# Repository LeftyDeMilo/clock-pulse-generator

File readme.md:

Breadboard Clock Pulse Generator with manual and automatic operating modes.
In manual mode the circuit operates as a debounced button. In automatic mode
it operates as a square wave generator. You could bear through a preset list
of frequencies in a range from 0.1 Hz to 97 Hz.

# Terminal

To check ATtiny24 fuses (and the MCU reaction) you could use `avrdude`.

```sh
$ avrdude -p t24 -c usbasp
```

Brandnew ATtiny24 _20SSU_ responses `Fuses OK (E:FF, H:DC, L:E2)`,
_20PU_ – `Fuses OK (E:FF, H:DF, L:62)`.

Preset fuses:

```sh
$ avrdude -p t24 -c usbasp -U lfuse:w:0xE2:m -U hfuse:w:0xDD:m -U efuse:w:0xFE:m
```

# Arduino IDE

Choose the proper MCU:

Tools > Board > DIY ATtiny > ATtiny24

Choose the compilation settings

Tools >

* Use Bootloader: "No (ISP Programmer Upload)"
* Processor Speed: "8MHz Internal Oscillator"
* Millis, Tone Support: "Millis Available, No Tone"
* Millis Accuracy: "Better Or Equal 0.1% Error (Highest Code Use)"
* Processor Version: "ATtiny24"
* Programmer: "DIY ATTiny: USBasp"

Upload sketch through ICSP connector using USBasp programmer:

Sketch > Upload Using Programmer

# Operating Manual

Use double click to change operating mode. In both modes an LED indicates a
voltage level on the PULSE pin.

### Manual mode

In manual mode the device operates as a debounced button. The seven segment
display indicates a voltage level on the PULSE pin (like an oscilloscope).

### Automatic Pulse Mode

In automatic pulse mode the display indicates a current pulse frequency.
You could bear though frequencies with a long button click.

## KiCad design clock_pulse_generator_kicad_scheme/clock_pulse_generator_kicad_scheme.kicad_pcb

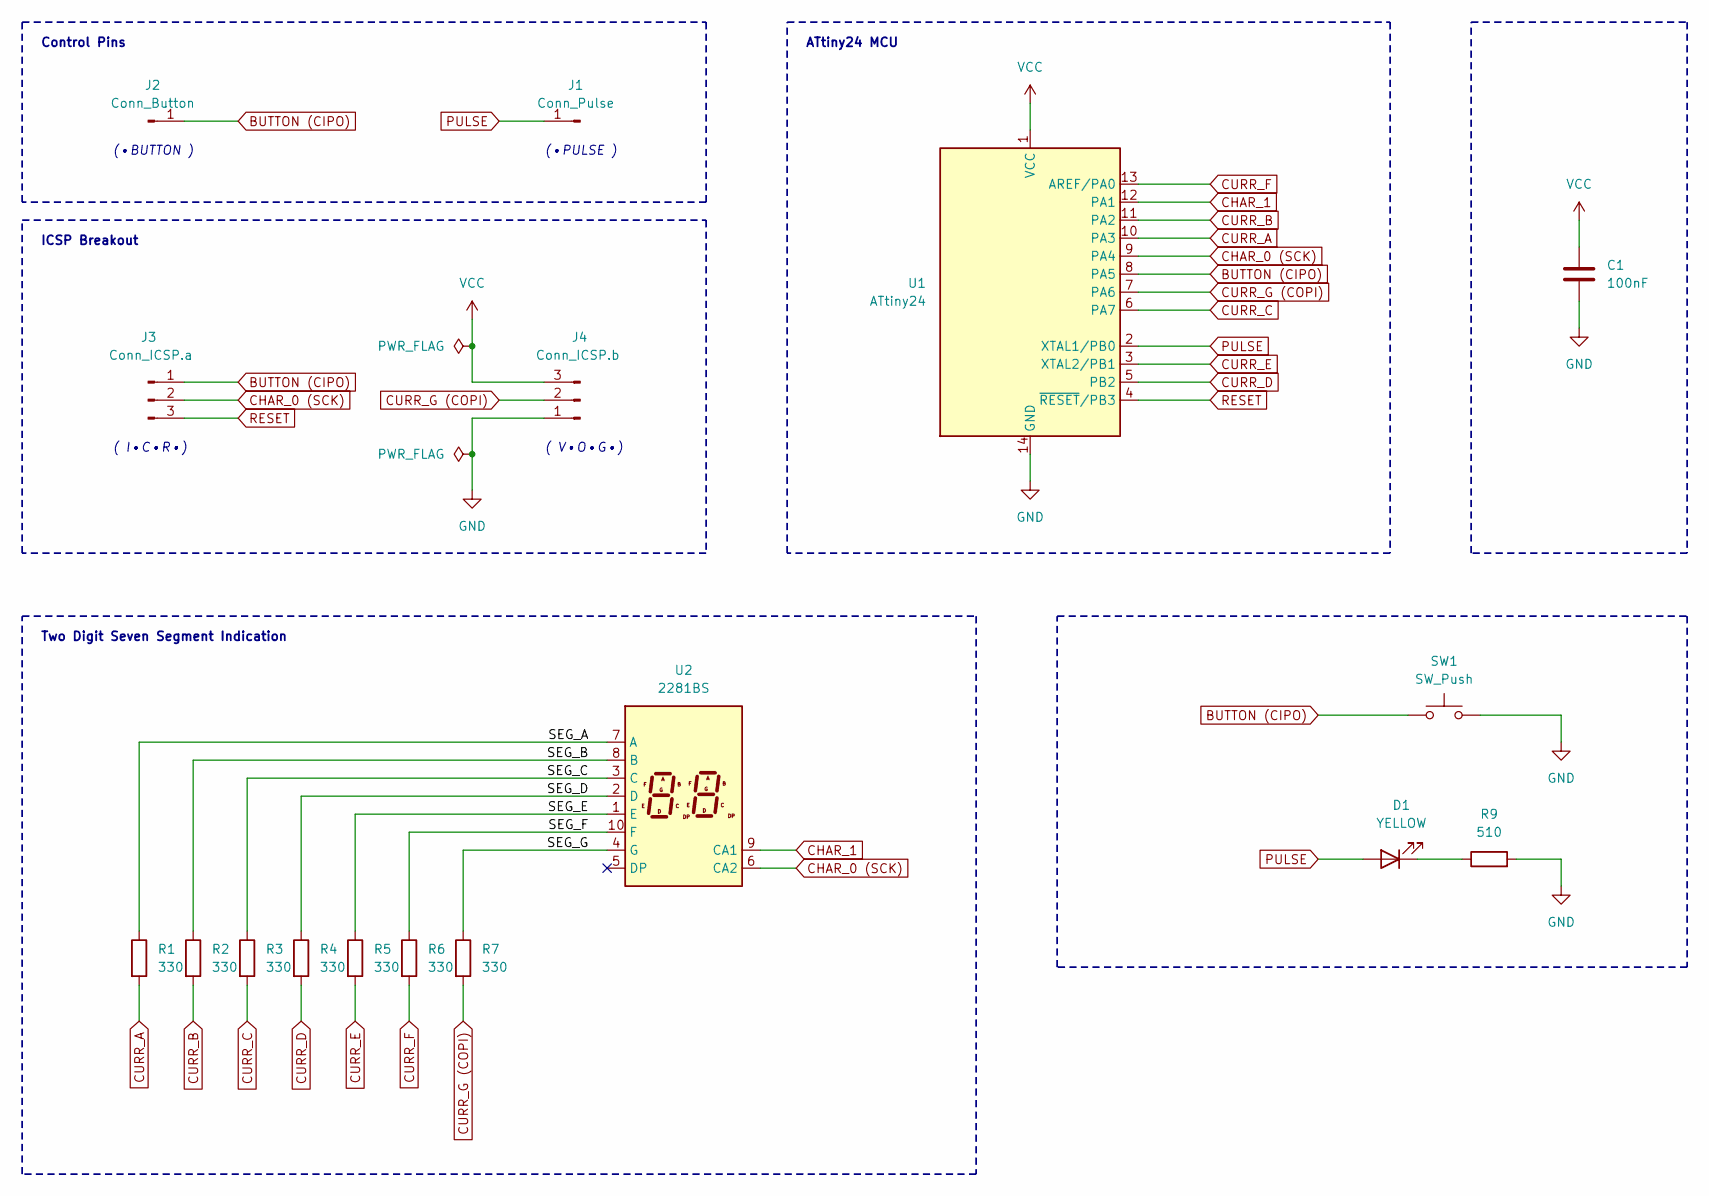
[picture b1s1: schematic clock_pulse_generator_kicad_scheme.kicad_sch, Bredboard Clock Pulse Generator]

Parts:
C1: 100nF; C_0805_2012Metric_Pad1.18x1.45mm_HandSolder
D1: YELLOW; LED_0805_2012Metric_Pad1.15x1.40mm_HandSolder
J1: Conn_Pulse; PinHeader_1x01_P2.54mm_Vertical
J2: Conn_Button; PinHeader_1x01_P2.54mm_Vertical
J3: Conn_ICSP.a; PinHeader_1x03_P2.54mm_Vertical
J4: Conn_ICSP.b; PinHeader_1x03_P2.54mm_Vertical
R1, R2, R3, R4, R5, R6, R7: 330; R_0805_2012Metric_Pad1.20x1.40mm_HandSolder
R9: 510; R_0805_2012Metric_Pad1.20x1.40mm_HandSolder
SW1: SW_Push; SW_PUSH_6mm_H5mm
U1: ATtiny24; SOIC-14_3.9x8.7mm_P1.27mm
U2: 2281BS; Sx39-1xxxxx

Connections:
/SEG_A: R1.1, U2.7 (A)
/SEG_B: R2.1, U2.8 (B)
/SEG_C: R3.1, U2.3 (C)
/SEG_D: R4.1, U2.2 (D)
/SEG_E: R5.1, U2.1 (E)
/SEG_F: R6.1, U2.10 (F)
/SEG_G: R7.1, U2.4 (G)
BUTTON (CIPO): J2.1, J3.1, SW1.1, U1.8 (PA5)
CHAR_0 (SCK): J3.2, U1.9 (PA4), U2.6 (CA2)
CHAR_1: U1.12 (PA1), U2.9 (CA1)
CURR_A: R1.2, U1.10 (PA3)
CURR_B: R2.2, U1.11 (PA2)
CURR_C: R3.2, U1.6 (PA7)
CURR_D: R4.2, U1.5 (PB2)
CURR_E: R5.2, U1.3 (XTAL2/PB1)
CURR_F: R6.2, U1.13 (AREF/PA0)
CURR_G (COPI): J4.2, R7.2, U1.7 (PA6)
GND: C1.2, J4.1, R9.2, SW1.2, U1.14 (GND)
unnamed: D1.1 (K), R9.1
PULSE: D1.2 (A), J1.1, U1.2 (XTAL1/PB0)
RESET: J3.3, U1.4 (~RESET/PB3)
VCC: C1.1, J4.3, U1.1 (VCC)

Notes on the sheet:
Control Pins
ICSP Breakout
ATtiny24 MCU
( V•O•G•)
(•BUTTON )
( I•C•R•)
(•PULSE )
Two Digit Seven Segment Indication

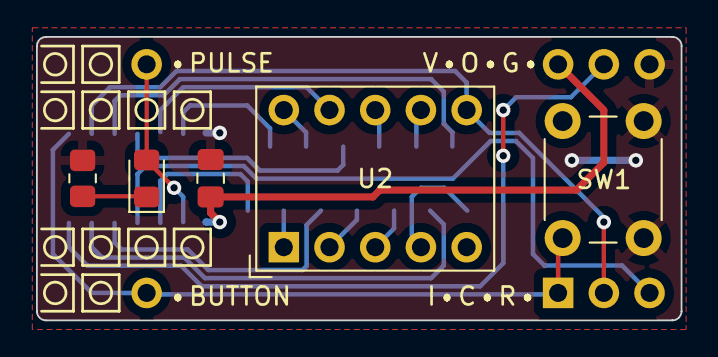
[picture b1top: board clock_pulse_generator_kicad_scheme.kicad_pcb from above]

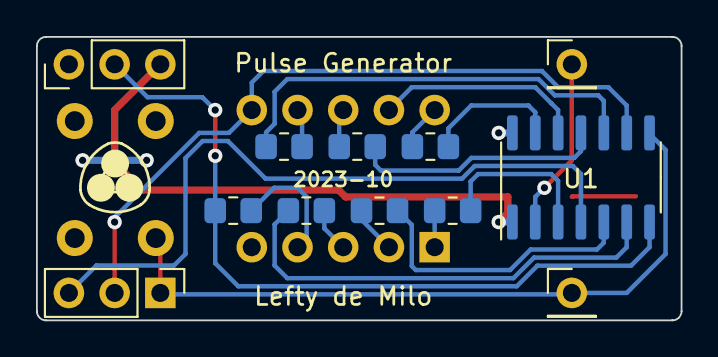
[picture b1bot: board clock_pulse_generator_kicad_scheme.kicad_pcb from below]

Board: 2 copper layers, 35.8 x 15.7 mm, 17 parts (12 on the bottom side), 22 nets.

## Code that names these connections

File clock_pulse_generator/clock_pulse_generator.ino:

/* ATtiny24 code
 *
 * Breadboard Clock Pulse Generator with manual and automatic operating modes.
 * In manual mode the circuit operates as a debounced button. In automatic mode
 * it operates as a square wave generator. You could bear through a preset list
 * of frequencies in a range from 0.1 Hz to 97 Hz.
 */

#include "globals.h"
#include "mcuHandler.h"
#include "displayHandler.h"
#include "buttonHandler.h"

void setup() {

  pinMode(mcu::BUTTON, INPUT_PULLUP);
  pinMode(mcu::OUTPUT_SIGNAL, OUTPUT);
  pinMode(mcu::SEG_a, OUTPUT);
  pinMode(mcu::SEG_b, OUTPUT);
  pinMode(mcu::SEG_c, OUTPUT);
  pinMode(mcu::SEG_d, OUTPUT);
  pinMode(mcu::SEG_e, OUTPUT);
  pinMode(mcu::SEG_f, OUTPUT);
  pinMode(mcu::SEG_g, OUTPUT);
  pinMode(mcu::CHAR_0, OUTPUT);
  pinMode(mcu::CHAR_1, OUTPUT);

  delay(1);

  // Manual mode indication
  display::setChars(symbol::OVERSCORE, symbol::OVERSCORE);

}

void loop() {

  button::handler();
  display::handler();

}
